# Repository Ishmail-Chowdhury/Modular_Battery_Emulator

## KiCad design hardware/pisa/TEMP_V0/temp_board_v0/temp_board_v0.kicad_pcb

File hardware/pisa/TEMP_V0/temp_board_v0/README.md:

# Pisa temperature card — TEMP-LAYOUT-1

Open `temp_board_v0.kicad_pro` in KiCad 10. The modern schematic and the **two-layer PCB** are synchronized with the selected temperature BOM. The board has **0 layout errors, 0 unrouted connections and 0 schematic-parity issues**, with 53 inherited library-definition warnings on retained footprints. ERC has 0 errors and 235 inherited off-grid drawing warnings. No rules were newly disabled.

All 34 fitted components are accounted for; no components or external mux were added. C2/U1/U3/U8 replacement footprints are installed and routed. Five components were relocated: C2, J6, C4, C9 and C11. The original card edge and outline are unchanged. J6 and the other optional headers remain DNP.

Readback of all eight DAC output voltages uses U1's internal analog selector and the populated bus-2 links R12/R18/R20. Temperature MISO exits **M1.34**, separate from CVE mux MISO on M1.33. For two boards, the two temperature returns must use separate FPGA inputs. No card/backplane patch wiring is required. The current Arty prototype has no temperature controller or pin allocation yet.

Current review: repository-root `docs/TEMPERATURE_LAYOUT_READBACK_2026_11_17.md`. Component datasheets and original-design discrepancies: `docs/TEMPERATURE_SCHEMATIC_REVIEW_2026_11_17.md` (historical schematic phase). Machine-readable checks and the BOM snapshot are in `docs/verification/temperature_layout_2026_11_17/`.

Run `tools/verify_temperature_layout.py` with KiCad's bundled Python. It requires the design folder, `--baseline-board`, `--baseline-netlist`, `--baseline-drc`, `--backplane`, `--bom`, `--output`, and optionally `--cli`. The documented baseline files in the verification folder allow the checks to be repeated.

This revision has not been fabricated or bench-qualified. Check actual connector/rack fit, including C2's 16 mm height, and qualify the CMU input bias, temperature curve and SPI timing during bring-up.

Original hardware author: University of Pisa Battery Lab. Baseline commit `a0d4499b8810e432f862b3f266d868523a92c2fc`; repository-root `TEMP_V0.rar` is retained unchanged. `legacy_reference/` preserves original source and stale purchasing exports; those exports are not the current BOM or fabrication package.

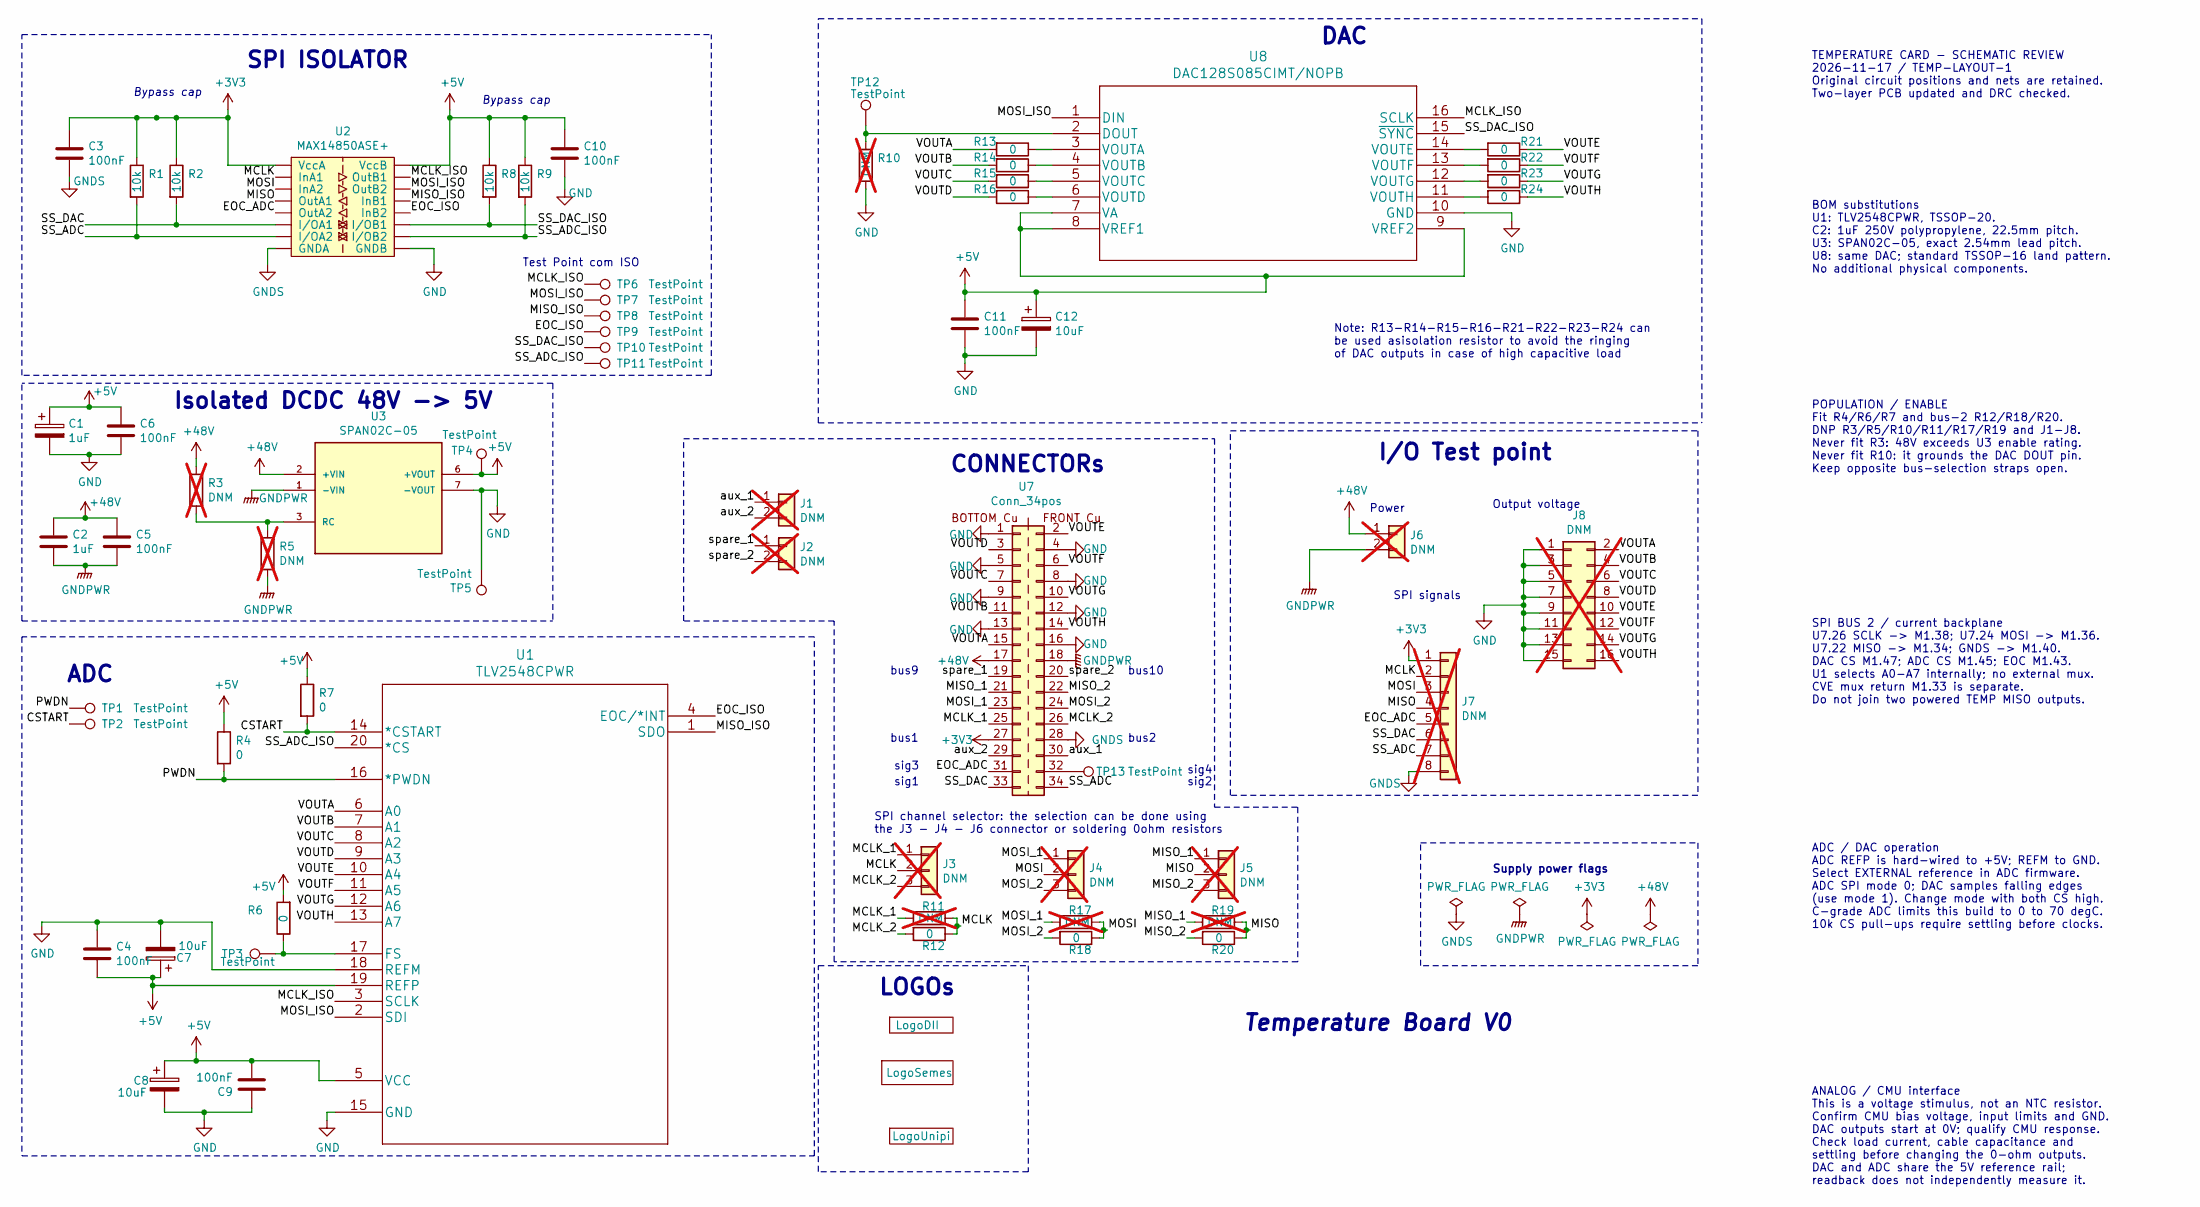
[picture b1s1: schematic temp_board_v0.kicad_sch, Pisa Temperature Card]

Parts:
C1: 1uF; CP_Elec_4x5.4; Rating 1uF / 50V; MPN 865060640001; JLCPCB C2163595
C2: 1uF; C_Rect_L26.5mm_W7.0mm_P22.50mm_MKS4; Rating 1uF / 250V PP; MPN R75IN410050H4J; JLCPCB C3787691
C3, C4, C6, C9, C10, C11: 100nF; C_0603_1608Metric_Pad1.08x0.95mm_HandSolder; Rating 100nF / 50V; MPN CC0603KRX7R9BB104; JLCPCB C14663
C5: 100nF; C_0805_2012Metric_Pad1.18x1.45mm_HandSolder; Rating 100nF / 100V; MPN CL21B104KCFNNNE; JLCPCB C28233
C7, C8, C12: 10uF; CP_Elec_4x5.4; Rating 10uF / 25V; MPN 865080440002; JLCPCB C2163477
J1, J2, J6: DNM; PinHeader_1x02_P2.54mm_Vertical; not fitted
J3, J4, J5: DNM; PinHeader_1x03_P2.54mm_Vertical; not fitted
J7: DNM; PinHeader_1x08_P2.54mm_Vertical; not fitted
J8: DNM; PinHeader_2x08_P2.54mm_Vertical; not fitted
R1, R2, R8, R9: 10k; R_0805_2012Metric_Pad1.20x1.40mm_HandSolder; MPN 0805W8F1002T5E; JLCPCB C17414
R3, R5, R10, R11, R17, R19: DNM; R_0805_2012Metric_Pad1.20x1.40mm_HandSolder; not fitted
R4, R6, R7, R12, R13, R14, R15, R16, R18, R20, R21, R22, R23, R24: 0; R_0805_2012Metric_Pad1.20x1.40mm_HandSolder; MPN 0805W8F0000T5E; JLCPCB C17477
TP1, TP2, TP3, TP4, TP5, TP6, TP7, TP8, TP9, TP10, TP11, TP12, TP13: TestPoint; PinHeader_1x01_P2.54mm_Vertical
U1: TLV2548CPWR; TSSOP-20_4.4x6.5mm_P0.65mm; MPN TLV2548CPWR; JLCPCB C2670506
U2: MAX14850ASE+; SOIC-16_3.9x9.9mm_P1.27mm; MPN MAX14850ASE+; Digikey PN MAX14850ASE+-ND
U3: SPAN02C-05; SPAN02C-05_SIP-8; PARTREV 1.0; JLCPCB C6681122
U4: LogoSemes; logo_semeslab_new_2
U5: LogoDII; logo_dii
U6: LogoUnipi; logo_cherubino
U7: Conn_34pos; Conn_34pos_Board
U8: DAC128S085CIMT/NOPB; TSSOP-16_4.4x5mm_P0.65mm; MPN DAC128S085CIMT/NOPB; JLCPCB C1554478

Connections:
+3V3: C3.1, J7.1, R1.1, R2.1, U2.1 (VccA), U7.27
+5V: C1.1, C4.2, C6.1, C7.1, C8.1, C9.2, C10.1, C11.1, C12.1, R4.1, R6.2, R7.1, R8.1, R9.1, TP4.1, U1.5 (VCC), U1.19 (REFP), U2.16 (VccB), U3.6 (+VOUT), U8.7 (VA), U8.8 (VREF1), U8.9 (VREF2)
+48V: C2.1, C5.1, J6.1, R3.1, U3.2 (+VIN), U7.17
/CSTART: R7.2, TP2.1, U1.14 (*CSTART)
/EOC_ADC: J7.5, U2.5 (OutA2), U7.31
/EOC_ISO: TP9.1, U1.4 (EOC/*INT), U2.12 (InB2)
/MCLK: J3.2, J7.2, R11.1, R12.1, U2.2 (InA1)
/MCLK_1: J3.1, R11.2, U7.25
/MCLK_2: J3.3, R12.2, U7.26
/MCLK_ISO: TP6.1, U1.3 (SCLK), U2.15 (OutB1), U8.16 (SCLK)
/MISO: J5.2, J7.4, R19.1, R20.1, U2.4 (OutA1)
/MISO_1: J5.1, R19.2, U7.21
/MISO_2: J5.3, R20.2, U7.22
/MISO_ISO: TP8.1, U1.1 (SDO), U2.13 (InB1)
/MOSI: J4.2, J7.3, R17.1, R18.1, U2.3 (InA2)
/MOSI_1: J4.1, R17.2, U7.23
/MOSI_2: J4.3, R18.2, U7.24
/MOSI_ISO: TP7.1, U1.2 (SDI), U2.14 (OutB2), U8.1 (DIN)
/PWDN: R4.2, TP1.1, U1.16 (*PWDN)
/SS_ADC: J7.7, R1.2, U2.7 (I/OA2), U7.34
/SS_ADC_ISO: R9.2, TP11.1, U1.20 (*CS), U2.10 (I/OB2)
/SS_DAC: J7.6, R2.2, U2.6 (I/OA1), U7.33
/SS_DAC_ISO: R8.2, TP10.1, U2.11 (I/OB1), U8.15 (~SYNC)
/VOUTA: J8.2, R13.2, U1.6 (A0), U7.15
/VOUTB: J8.4, R14.2, U1.7 (A1), U7.11
/VOUTC: J8.6, R15.2, U1.8 (A2), U7.7
/VOUTD: J8.8, R16.2, U1.9 (A3), U7.3
/VOUTE: J8.10, R21.1, U1.10 (A4), U7.2
/VOUTF: J8.12, R22.1, U1.11 (A5), U7.6
/VOUTG: J8.14, R23.1, U1.12 (A6), U7.10
/VOUTH: J8.16, R24.1, U1.13 (A7), U7.14
/aux_1: J1.1, U7.30
/aux_2: J1.2, U7.29
/spare_1: J2.1, U7.19
/spare_2: J2.2, U7.20
GND: C1.2, C4.1, C6.2, C7.2, C8.2, C9.1, C10.2, C11.2, C12.2, J8.1, J8.3, J8.5, J8.7, J8.9, J8.11, J8.13, J8.15, R10.2, TP5.1, U1.15 (GND), U1.18 (REFM), U2.9 (GNDB), U3.7 (-VOUT), U7.1, U7.4, U7.5, U7.8, U7.9, U7.12, U7.13, U7.16, U8.10 (GND)
GNDPWR: C2.2, C5.2, J6.2, R5.2, U3.1 (-VIN), U7.18
GNDS: C3.2, J7.8, U2.8 (GNDA), U7.28
unnamed: TP13.1, U7.32
unnamed: R6.1, TP3.1, U1.17 (FS)
unnamed: R3.2, R5.1, U3.3 (RC)
unnamed: R10.1, TP12.1, U8.2 (DOUT)
unnamed: R13.1, U8.3 (VOUTA)
unnamed: R14.1, U8.4 (VOUTB)
unnamed: R15.1, U8.5 (VOUTC)
unnamed: R16.1, U8.6 (VOUTD)
unnamed: R21.2, U8.14 (VOUTE)
unnamed: R22.2, U8.13 (VOUTF)
unnamed: R23.2, U8.12 (VOUTG)
unnamed: R24.2, U8.11 (VOUTH)

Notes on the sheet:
bus1
Test Point com ISO
Output voltage
Bypass cap
Temperature Board V0
bus9
sig1
LOGOs
bus2
Note: R13-R14-R15-R16-R21-R22-R23-R24 can be used asisolation resistor to avoid the ringing of DAC outputs in case of high capacitive load
I/O Test point
SPI ISOLATOR
sig2
SPI signals
sig3
CONNECTORs
bus10
SPI channel selector: the selection can be done using the J3 - J4 - J6 connector or soldering 0ohm resistors
Power
Isolated DCDC 48V -> 5V
Supply power flags
ADC
sig4
DAC
TEMPERATURE CARD - SCHEMATIC REVIEW 2026-11-17 / TEMP-LAYOUT-1 Original circuit positions and nets are retained. Two-layer PCB updated and DRC checked.
BOM substitutions U1: TLV2548CPWR, TSSOP-20. C2: 1uF 250V polypropylene, 22.5mm pitch. U3: SPAN02C-05, exact 2.54mm lead pitch. U8: same DAC; standard TSSOP-16 land pattern. No additional physical components.
POPULATION / ENABLE Fit R4/R6/R7 and bus-2 R12/R18/R20. DNP R3/R5/R10/R11/R17/R19 and J1-J8. Never fit R3: 48V exceeds U3 enable rating. Never fit R10: it grounds the DAC DOUT pin. Keep opposite bus-selection straps open.
SPI BUS 2 / current backplane U7.26 SCLK -> M1.38; U7.24 MOSI -> M1.36. U7.22 MISO -> M1.34; GNDS -> M1.40. DAC CS M1.47; ADC CS M1.45; EOC M1.43. U1 selects A0-A7 internally; no external mux. CVE mux return M1.33 is separate. Do not join two powered TEMP MISO outputs.
ADC / DAC operation ADC REFP is hard-wired to +5V; REFM to GND. Select EXTERNAL reference in ADC firmware. ADC SPI mode 0; DAC samples falling edges (use mode 1). Change mode with both CS high. C-grade ADC limits this build to 0 to 70 degC. 10k CS pull-ups require settling before clocks.
ANALOG / CMU interface This is a voltage stimulus, not an NTC resistor. Confirm CMU bias voltage, input limits and GND. DAC outputs start at 0V; qualify CMU response. Check load current, cable capacitance and settling before changing the 0-ohm outputs. DAC and ADC share the 5V reference rail; readb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

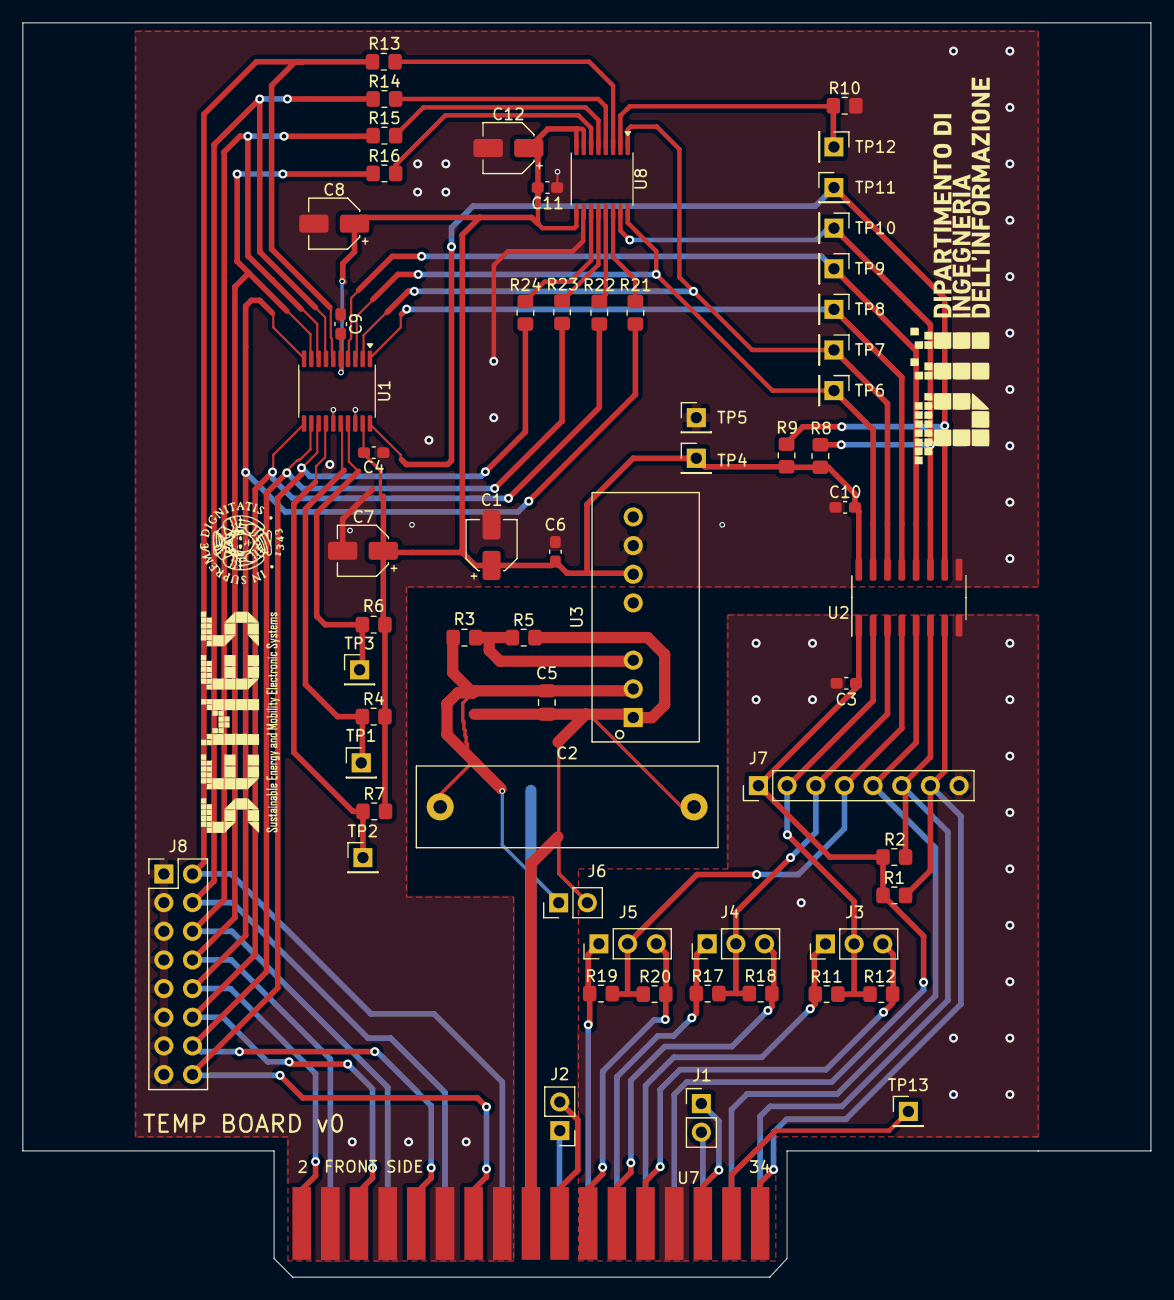
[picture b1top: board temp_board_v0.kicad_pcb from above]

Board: 2 copper layers, 100.0 x 111.2 mm, 65 parts (0 on the bottom side), 50 nets.

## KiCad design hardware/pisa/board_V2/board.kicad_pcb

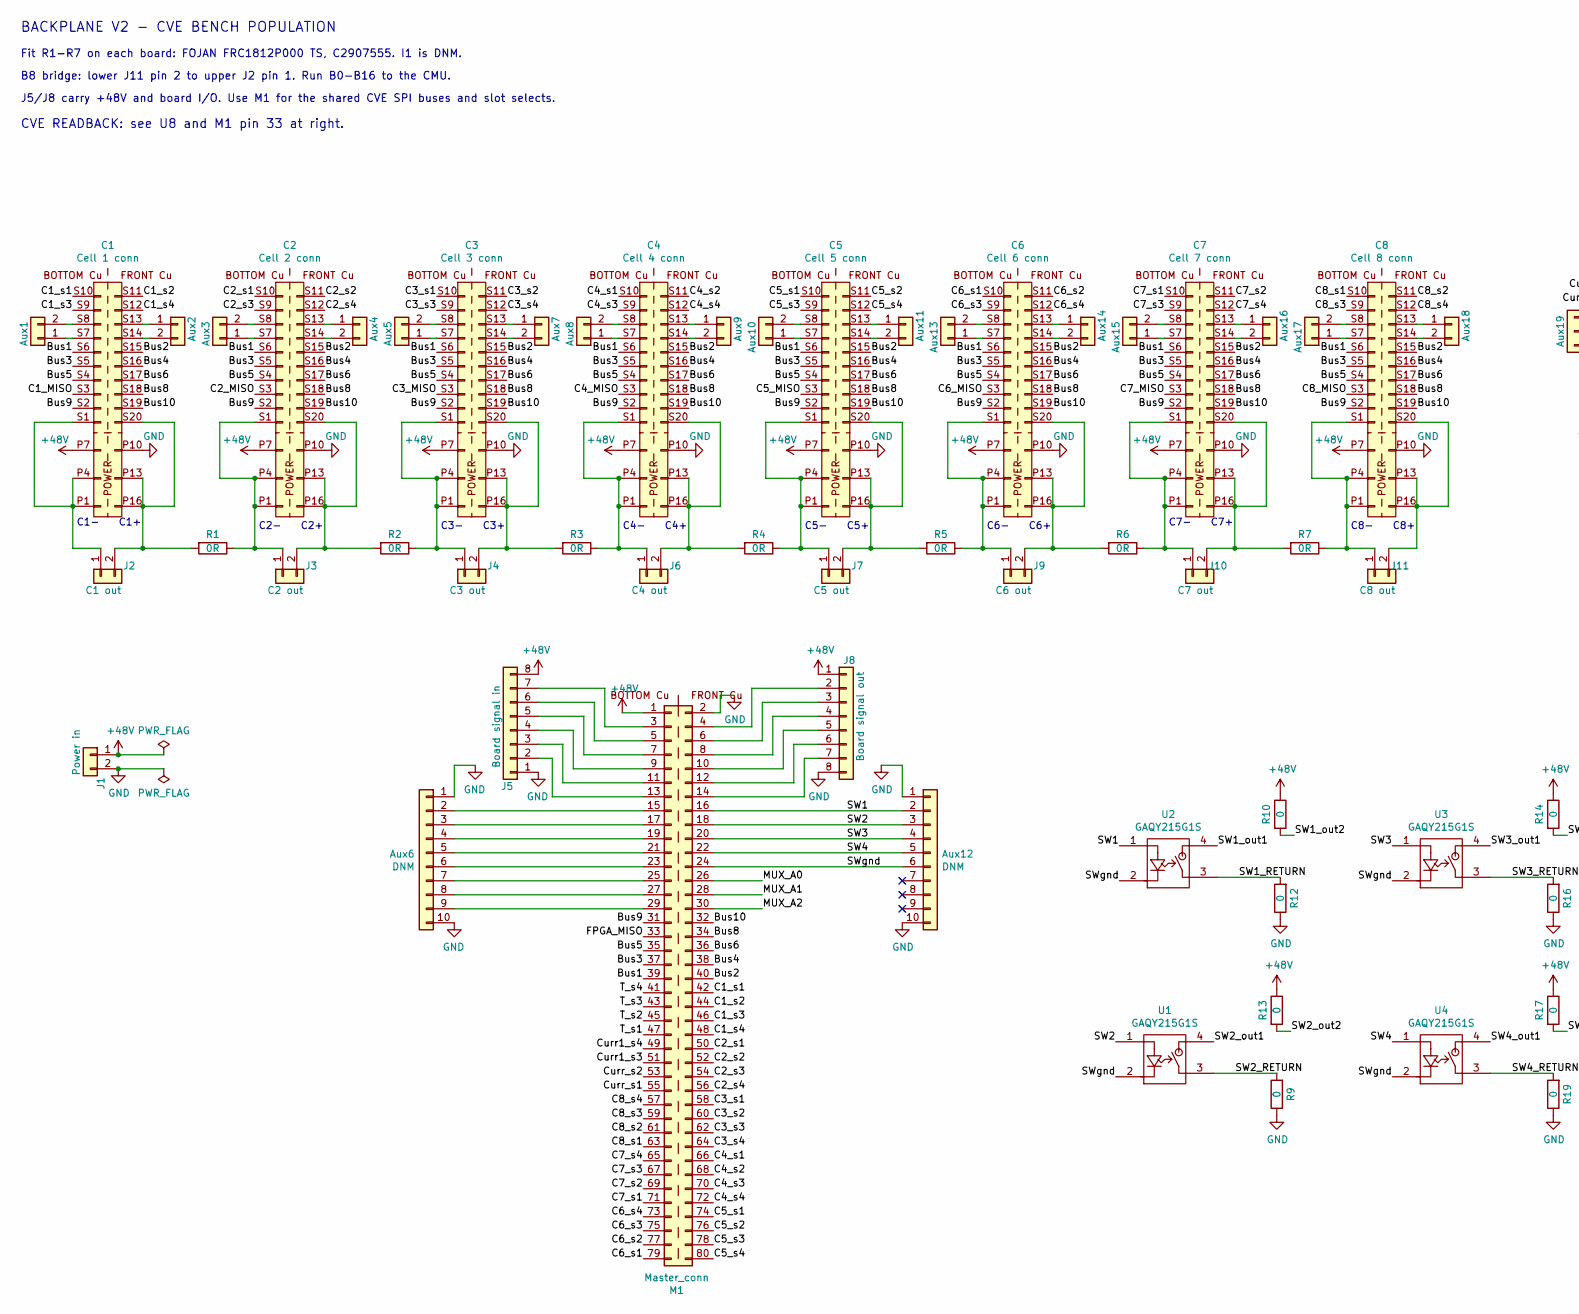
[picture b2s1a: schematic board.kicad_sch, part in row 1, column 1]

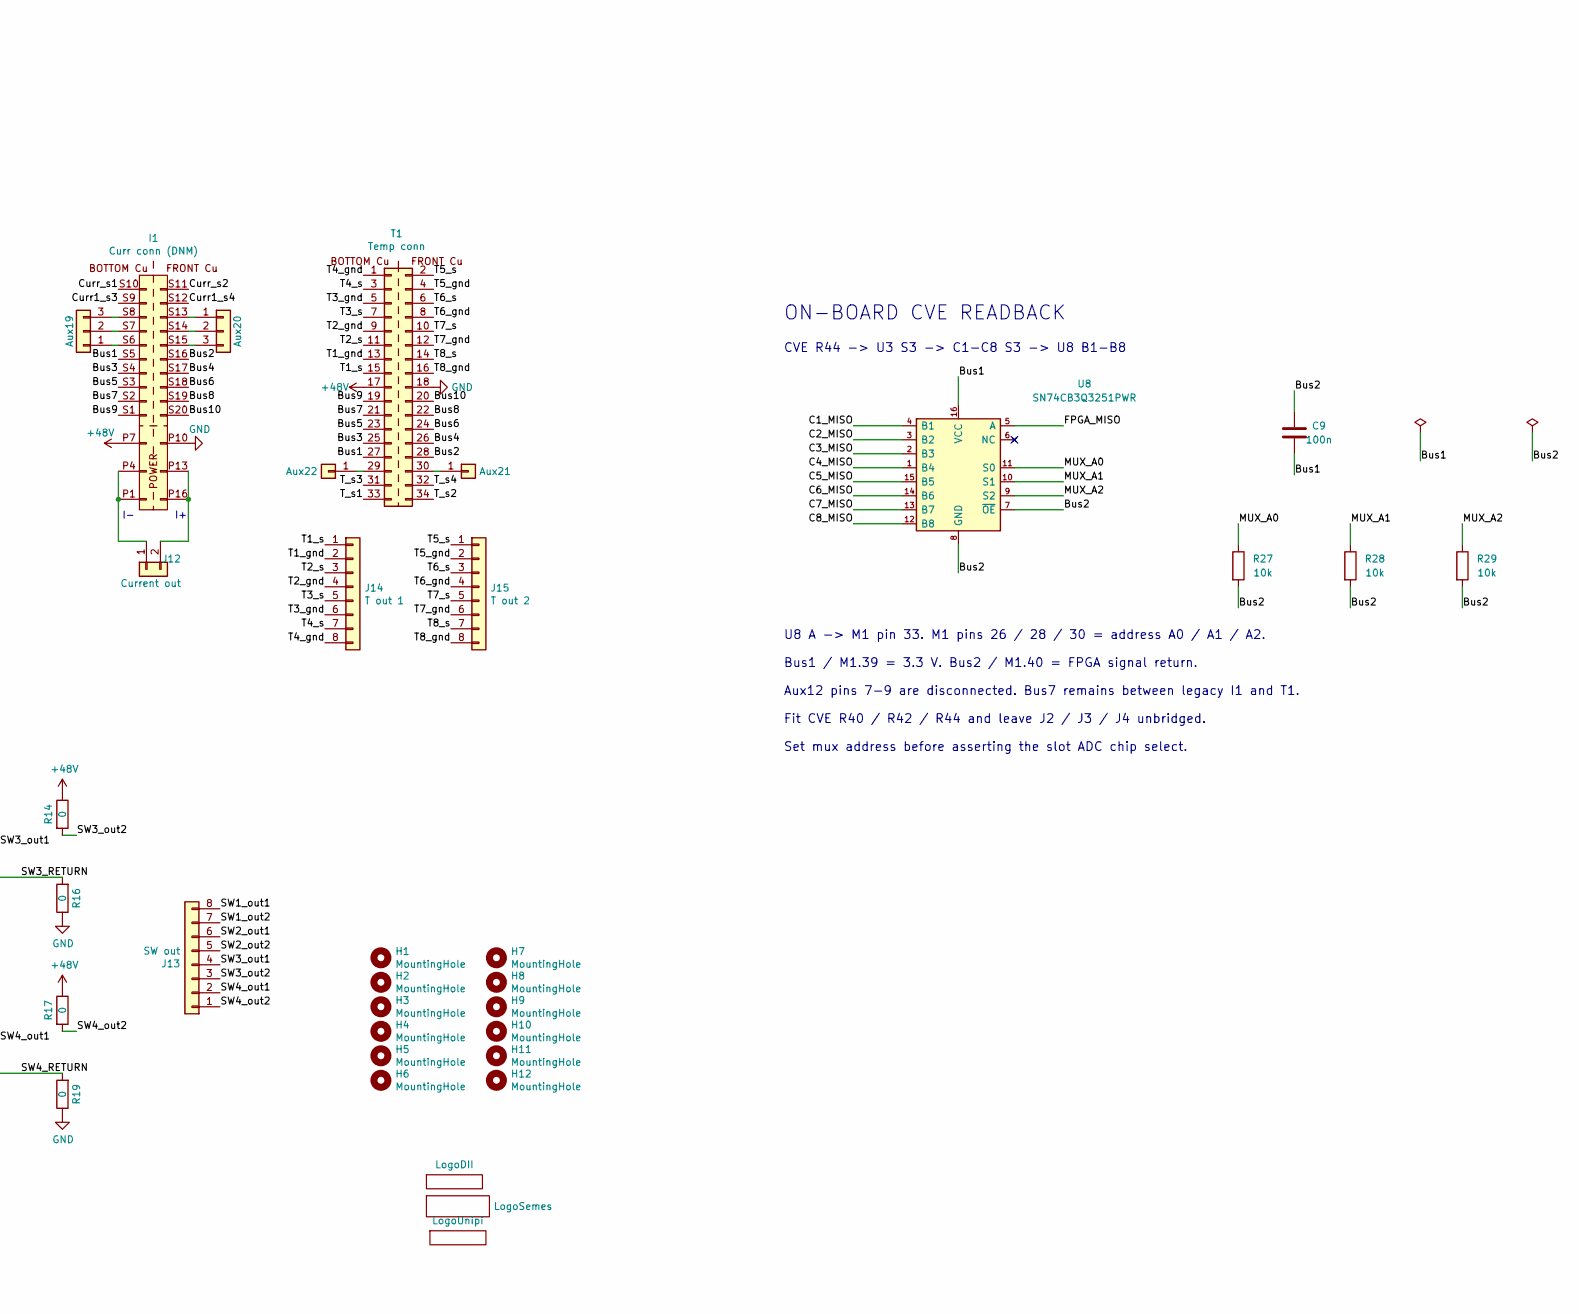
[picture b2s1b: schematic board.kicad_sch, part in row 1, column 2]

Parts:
Aux1, Aux2, Aux3, Aux4, Aux5, Aux7, Aux8, Aux9, Aux10, Aux11, Aux13, Aux14, Aux15, Aux16, Aux17, Aux18: DNM; Socket_Strip_Straight_1x02_Pitch2.54mm
Aux6, Aux12: DNM; Socket_Strip_Straight_1x10_Pitch2.54mm
Aux19, Aux20: DNM; Socket_Strip_Straight_1x03_Pitch2.54mm
Aux21, Aux22: DNM; Socket_Strip_Straight_1x01_Pitch2.54mm
C1: Cell 1 conn; Conn_26pos_Head
C2: Cell 2 conn; Conn_26pos_Head
C3: Cell 3 conn; Conn_26pos_Head
C4: Cell 4 conn; Conn_26pos_Head
C5: Cell 5 conn; Conn_26pos_Head
C6: Cell 6 conn; Conn_26pos_Head
C7: Cell 7 conn; Conn_26pos_Head
C8: Cell 8 conn; Conn_26pos_Head
C9: 100n; C_0603_1608Metric; MPN CL10B104KB8NNNC; JLCPCB C1591
H1, H2, H3, H4, H5, H6, H7, H8, H9, H10, H11, H12: MountingHole; MountingHole_3.2mm_M3
I1: Curr conn (DNM); Conn_26pos_Head
J1: Power in; 691137710002; JLCPCB C474881
J2: C1 out; 691137710002; JLCPCB C474881
J3: C2 out; 691137710002; JLCPCB C474881
J4: C3 out; 691137710002; JLCPCB C474881
J5: Board signal in; 691402910008B; JLCPCB C915917
J6: C4 out; 691137710002; JLCPCB C474881
J7: C5 out; 691137710002; JLCPCB C474881
J8: Board signal out; 691402910008B; JLCPCB C915917
J9: C6 out; 691137710002; JLCPCB C474881
J10: C7 out; 691137710002; JLCPCB C474881
J11: C8 out; 691137710002; JLCPCB C474881
J12: Current out; 691137710002; JLCPCB C474881
J13: SW out; 691402910008B; JLCPCB C915917
J14: T out 1; 691402910008B; JLCPCB C915917
J15: T out 2; 691402910008B; JLCPCB C915917
M1: Master_conn; Conn_80pos_Head
R1, R2, R3, R4, R5, R6, R7: 0R; R_1812_HandSoldering; JLCPCB C2907555
R9, R10, R12, R13, R14, R16, R17, R19: 0; R_0805_HandSoldering; JLCPCB C17477
R27, R28, R29: 10k; R_0603_1608Metric; MPN 0603WAF1002T5E; JLCPCB C25804
T1: Temp conn; Conn_34pos_Head; JLCPCB C4801357
U1, U2, U3, U4: GAQY215G1S; GAQY215G1S_SOP-4; JLCPCB C22385004
U5: LogoDII; logo_dii
U6: LogoSemes; logo_semeslab_new_2
U7: LogoUnipi; logo_cherubino
U8: SN74CB3Q3251PWR; TSSOP-16_4.4x5mm_P0.65mm; MPN SN74CB3Q3251PWR

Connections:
+48V: C1.P7, C2.P7, C3.P7, C4.P7, C5.P7, C6.P7, C7.P7, C8.P7, I1.P7, J1.1, J5.8, J8.1, M1.1, R10.1, R13.1, R14.1, R17.1, T1.17
/Bus1: C1.S6, C2.S6, C3.S6, C4.S6, C5.S6, C6.S6, C7.S6, C8.S6, C9.2, I1.S5, M1.39, T1.27, U8.16 (VCC)
/Bus2: C1.S15, C2.S15, C3.S15, C4.S15, C5.S15, C6.S15, C7.S15, C8.S15, C9.1, I1.S16, M1.40, R27.2, R28.2, R29.2, T1.28, U8.7 (~OE), U8.8 (GND)
/Bus3: C1.S5, C2.S5, C3.S5, C4.S5, C5.S5, C6.S5, C7.S5, C8.S5, I1.S4, M1.37, T1.25
/Bus4: C1.S16, C2.S16, C3.S16, C4.S16, C5.S16, C6.S16, C7.S16, C8.S16, I1.S17, M1.38, T1.26
/Bus5: C1.S4, C2.S4, C3.S4, C4.S4, C5.S4, C6.S4, C7.S4, C8.S4, I1.S3, M1.35, T1.23
/Bus6: C1.S17, C2.S17, C3.S17, C4.S17, C5.S17, C6.S17, C7.S17, C8.S17, I1.S18, M1.36, T1.24
/Bus7: I1.S2, T1.21
/Bus8: C1.S18, C2.S18, C3.S18, C4.S18, C5.S18, C6.S18, C7.S18, C8.S18, I1.S19, M1.34, T1.22
/Bus9: C1.S2, C2.S2, C3.S2, C4.S2, C5.S2, C6.S2, C7.S2, C8.S2, I1.S1, M1.31, T1.19
/Bus10: C1.S19, C2.S19, C3.S19, C4.S19, C5.S19, C6.S19, C7.S19, C8.S19, I1.S20, M1.32, T1.20
/C1_MISO: C1.S3, U8.4 (B1)
/C1_s1: C1.S10, M1.42
/C1_s2: C1.S11, M1.44
/C1_s3: C1.S9, M1.46
/C1_s4: C1.S12, M1.48
/C2_MISO: C2.S3, U8.3 (B2)
/C2_s1: C2.S10, M1.50
/C2_s2: C2.S11, M1.52
/C2_s3: C2.S9, M1.54
/C2_s4: C2.S12, M1.56
/C3_MISO: C3.S3, U8.2 (B3)
/C3_s1: C3.S10, M1.58
/C3_s2: C3.S11, M1.60
/C3_s3: C3.S9, M1.62
/C3_s4: C3.S12, M1.64
/C4_MISO: C4.S3, U8.1 (B4)
/C4_s1: C4.S10, M1.66
/C4_s2: C4.S11, M1.68
/C4_s3: C4.S9, M1.70
/C4_s4: C4.S12, M1.72
/C5_MISO: C5.S3, U8.15 (B5)
/C5_s1: C5.S10, M1.74
/C5_s2: C5.S11, M1.76
/C5_s3: C5.S9, M1.78
/C5_s4: C5.S12, M1.80
/C6_MISO: C6.S3, U8.14 (B6)
/C6_s1: C6.S10, M1.79
/C6_s2: C6.S11, M1.77
/C6_s3: C6.S9, M1.75
/C6_s4: C6.S12, M1.73
/C7_MISO: C7.S3, U8.13 (B7)
/C7_s1: C7.S10, M1.71
/C7_s2: C7.S11, M1.69
/C7_s3: C7.S9, M1.67
/C7_s4: C7.S12, M1.65
/C8_MISO: C8.S3, U8.12 (B8)
/C8_s1: C8.S10, M1.63
/C8_s2: C8.S11, M1.61
/C8_s3: C8.S9, M1.59
/C8_s4: C8.S12, M1.57
/Curr1_s3: I1.S9, M1.51
/Curr1_s4: I1.S12, M1.49
/Curr_s1: I1.S10, M1.55
/Curr_s2: I1.S11, M1.53
/FPGA_MISO: M1.33, U8.5 (A)
/MUX_A0: M1.26, R27.1, U8.11 (S0)
/MUX_A1: M1.28, R28.1, U8.10 (S1)
/MUX_A2: M1.30, R29.1, U8.9 (S2)
/SW1: Aux12.2, M1.16, U2.1
/SW1_RETURN: R12.2, U2.3
/SW1_out1: J13.8, U2.4
/SW1_out2: J13.7, R10.2
/SW2: Aux12.3, M1.18, U1.1
/SW2_RETURN: R9.2, U1.3
/SW2_out1: J13.6, U1.4
/SW2_out2: J13.5, R13.2
/SW3: Aux12.4, M1.20, U3.1
/SW3_RETURN: R16.2, U3.3
/SW3_out1: J13.4, U3.4
/SW3_out2: J13.3, R14.2
/SW4: Aux12.5, M1.22, U4.1
/SW4_RETURN: R19.2, U4.3
/SW4_out1: J13.2, U4.4
/SW4_out2: J13.1, R17.2
/SWgnd: Aux12.6, M1.24, U1.2, U2.2, U3.2, U4.2
/T1_gnd: J14.2, T1.13
/T1_s: J14.1, T1.15
/T2_gnd: J14.4, T1.9
/T2_s: J14.3, T1.11
/T3_gnd: J14.6, T1.5
/T3_s: J14.5, T1.7
/T4_gnd: J14.8, T1.1
/T4_s: J14.7, T1.3
/T5_gnd: J15.2, T1.4
/T5_s: J15.1, T1.2
/T6_gnd: J15.4, T1.8
/T6_s: J15.3, T1.6
/T7_gnd: J15.6, T1.12
/T7_s: J15.5, T1.10
/T8_gnd: J15.8, T1.16
/T8_s: J15.7, T1.14
/T_s1: M1.47, T1.33
/T_s2: M1.45, T1.34
/T_s3: M1.43, T1.31
/T_s4: M1.41, T1.32
GND: Aux6.1, Aux6.10, Aux12.1, Aux12.10, C1.P10, C2.P10, C3.P10, C4.P10, C5.P10, C6.P10, C7.P10, C8.P10, I1.P10, J1.2, J5.1, J8.8, M1.2, R9.1, R12.1, R16.1, R19.1, T1.18
unnamed: Aux1.1, C1.S7
unnamed: Aux1.2, C1.S8
unnamed: Aux2.1, C1.S13
unnamed: Aux2.2, C1.S14
unnamed: Aux3.1, C2.S7
unnamed: Aux3.2, C2.S8
unnamed: Aux4.1, C2.S13
unnamed: Aux4.2, C2.S14
unnamed: Aux5.1, C3.S7
unnamed: Aux5.2, C3.S8
unnamed: Aux6.2, M1.15
unnamed: Aux6.3, M1.17
unnamed: Aux6.4, M1.19
unnamed: Aux6.5, M1.21
unnamed: Aux6.6, M1.23
unnamed: Aux6.7, M1.25
unnamed: Aux6.8, M1.27
unnamed: Aux6.9, M1.29
unnamed: Aux7.1, C3.S13
unnamed: Aux7.2, C3.S14
unnamed: Aux8.1, C4.S7
unnamed: Aux8.2, C4.S8
unnamed: Aux9.1, C4.S13
unnamed: Aux9.2, C4.S14
unnamed: Aux10.1, C5.S7
unnamed: Aux10.2, C5.S8
unnamed: Aux11.1, C5.S13
unnamed: Aux11.2, C5.S14
unnamed: Aux13.1, C6.S7
unnamed: Aux13.2, C6.S8
unnamed: Aux14.1, C6.S13
unnamed: Aux14.2, C6.S14
unnamed: Aux15.1, C7.S7
unnamed: Aux15.2, C7.S8
unnamed: Aux16.1, C7.S13
unnamed: Aux16.2, C7.S14
unnamed: Aux17.1, C8.S7
unnamed: Aux17.2, C8.S8
unnamed: Aux18.1, C8.S13
unnamed: Aux18.2, C8.S14
unnamed: Aux19.1, I1.S6
unnamed: Aux19.2, I1.S7
unnamed: Aux19.3, I1.S8
unnamed: Aux20.1, I1.S13
unnamed: Aux20.2, I1.S14
unnamed: Aux20.3, I1.S15
unnamed: Aux21.1, T1.30
unnamed: Aux22.1, T1.29
unnamed: C1.P1, C1.P4, C1.S1, J2.1
unnamed: C1.P13, C1.P16, C1.S20, J2.2, R1.2
unnamed: C2.P1, C2.P4, C2.S1, J3.1, R1.1
unnamed: C2.P13, C2.P16, C2.S20, J3.2, R2.2
unnamed: C3.P1, C3.P4, C3.S1, J4.1, R2.1
unnamed: C3.P13, C3.P16, C3.S20, J4.2, R3.2
unnamed: J5.2, M1.13
unnamed: J5.3, M1.11
unnamed: J5.4, M1.9
unnamed: J5.5, M1.7
unnamed: J5.6, M1.5
unnamed: J5.7, M1.3
unnamed: C4.P1, C4.P4, C4.S1, J6.1, R3.1
unnamed: C4.P13, C4.P16, C4.S20, J6.2, R4.2
unnamed: C5.P1, C5.P4, C5.S1, J7.1, R4.1
unnamed: C5.P13, C5.P16, C5.S20, J7.2, R5.2
unnamed: J8.2, M1.4
unnamed: J8.3, M1.6
unnamed: J8.4, M1.8
unnamed: J8.5, M1.10
unnamed: J8.6, M1.12
unnamed: J8.7, M1.14
unnamed: C6.P1, C6.P4, C6.S1, J9.1, R5.1
unnamed: C6.P13, C6.P16, C6.S20, J9.2, R6.2
unnamed: C7.P1, C7.P4, C7.S1, J10.1, R6.1
unnamed: C7.P13, C7.P16, C7.S20, J10.2, R7.2
unnamed: C8.P1, C8.P4, C8.S1, J11.1, R7.1
unnamed: C8.P13, C8.P16, C8.S20, J11.2
unnamed: I1.P1, I1.P4, J12.1
unnamed: I1.P13, I1.P16, J12.2

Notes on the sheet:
C2+
C7-
C4+
C8-
C3+
C7+
C6+
C1-
C2-
C4-
C3-
BACKPLANE V2 - CVE BENCH POPULATION
C5-
B8 bridge: lower J11 pin 2 to upper J2 pin 1. Run B0-B16 to the CMU.
C5+
C8+
Fit R1-R7 on each board: FOJAN FRC1812P000 TS, C2907555. I1 is DNM.
C6-
J5/J8 carry +48V and board I/O. Use M1 for the shared CVE SPI buses and slot selects.
C1+
ON-BOARD CVE READBACK
CVE R44 -> U3 S3 -> C1-C8 S3 -> U8 B1-B8
U8 A -> M1 pin 33. M1 pins 26 / 28 / 30 = address A0 / A1 / A2.
Bus1 / M1.39 = 3.3 V. Bus2 / M1.40 = FPGA signal return.
Aux12 pins 7-9 are disconnected. Bus7 remains between legacy I1 and T1.
Fit CVE R40 / R42 / R44 and leave J2 / J3 / J4 unbridged.
Set mux address before asserting the slot ADC chip select.
CVE READBACK: see U8 and M1 pin 33 at right.

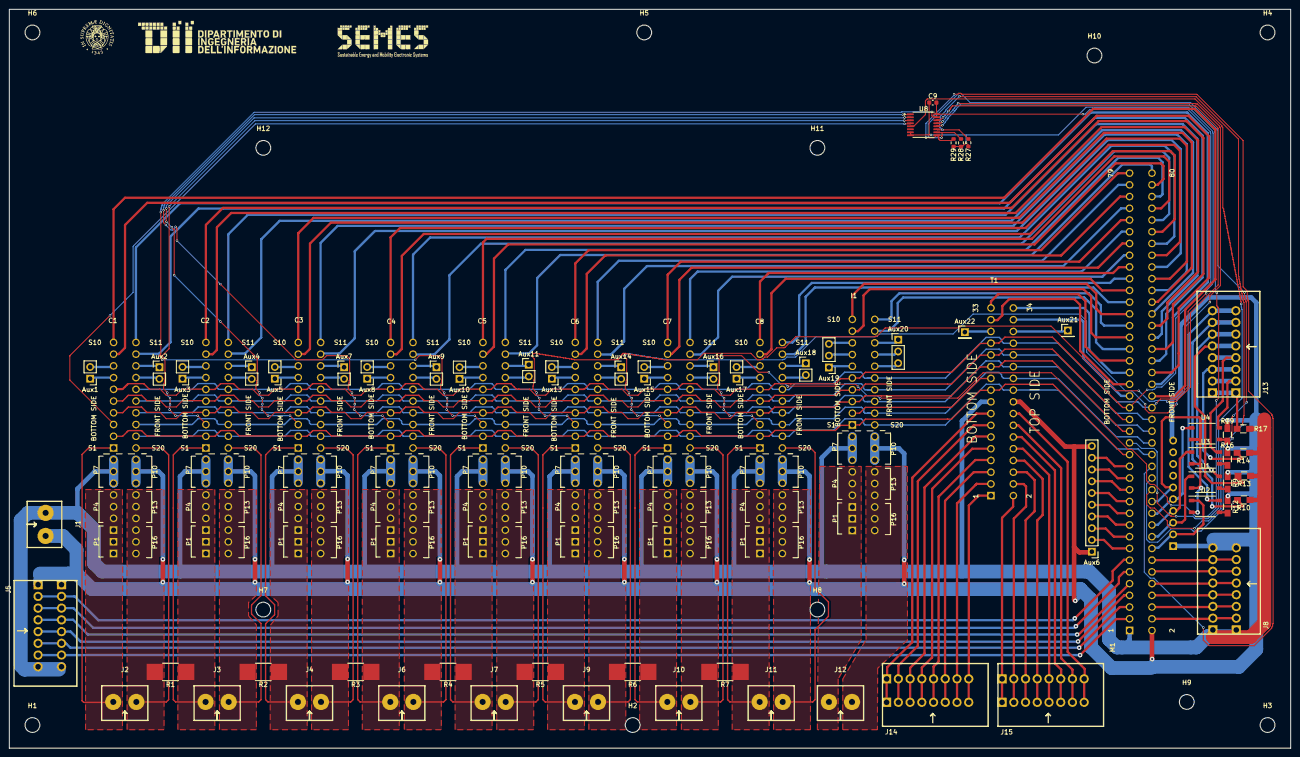
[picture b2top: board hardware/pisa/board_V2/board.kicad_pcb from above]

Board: 2 copper layers, 277.5 x 160.0 mm, 87 parts (1 on the bottom side), 175 nets.

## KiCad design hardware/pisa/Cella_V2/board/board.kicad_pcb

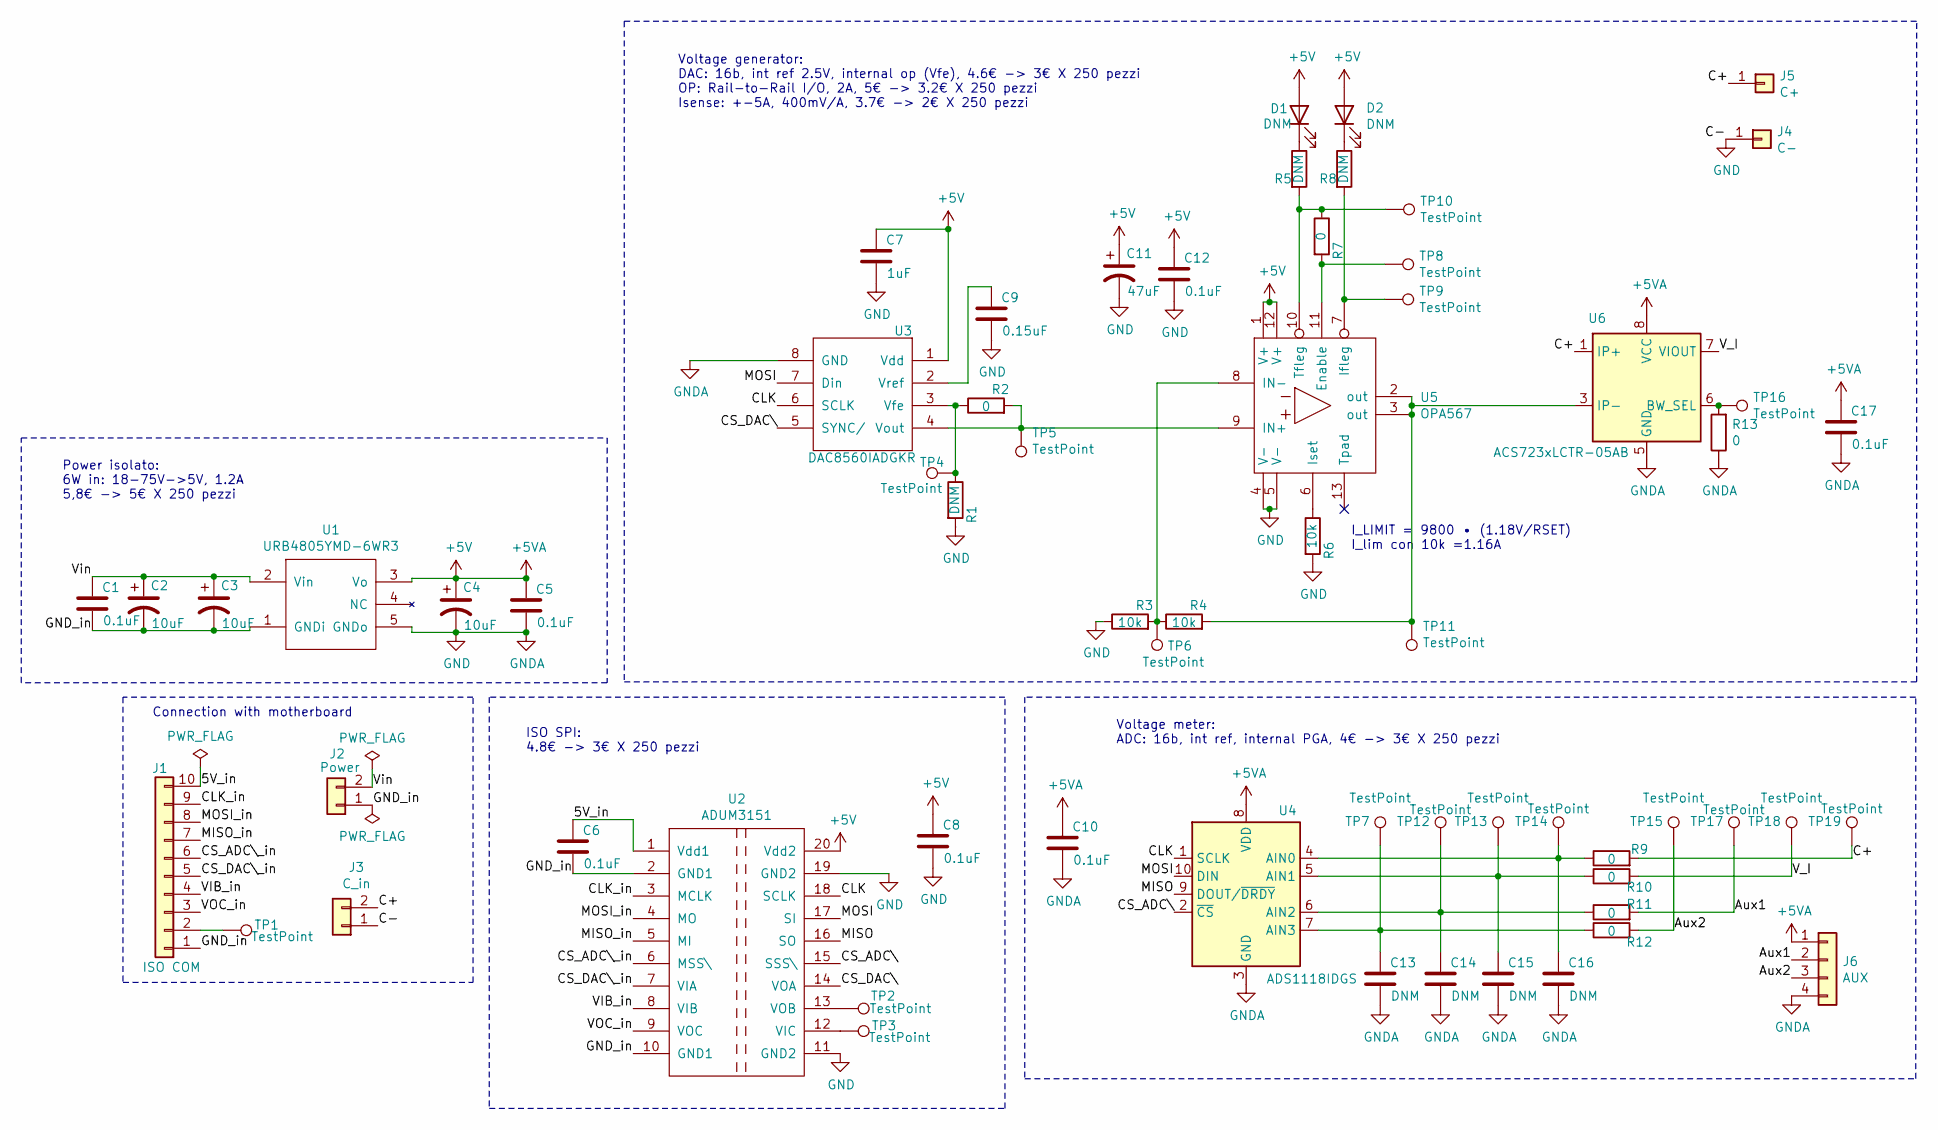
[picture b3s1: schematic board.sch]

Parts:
C1, C5, C6, C8, C10, C12, C17: 0.1uF; C_0805_HandSoldering; Digi 1276-6840-1-ND
C2, C3, C4: 10uF; CP_Elec_6.3x7.7; Digi 399-18132-1-ND
C7: 1uF; C_0805_HandSoldering; Digi 1276-6471-1-ND
C9: 0.15uF; C_0805_HandSoldering; Digi 1276-6476-1-ND
C11: 47uF; CP_Elec_10x10.5; Digi 493-9631-1-ND
C13, C14, C15, C16: DNM; C_0805_HandSoldering; Digi 1276-6840-1-ND
D1, D2: DNM; D_0805
J1: ISO COM; Pin_Header_Straight_1x10_Pitch2.54mm
J2: Power; Pin_Header_Straight_1x02_Pitch2.54mm
J3: C_in; Pin_Header_Straight_1x02_Pitch2.54mm
J4: C-; Banana_Jack_1Pin
J5: C+; Banana_Jack_1Pin
J6: AUX; Pin_Header_Straight_1x04_Pitch2.54mm
R1, R5, R8: DNM; C_0805_HandSoldering
R2, R7, R9, R10, R11, R12, R13: 0; C_0805_HandSoldering
R3, R4, R6: 10k; C_0805_HandSoldering; Digi P10KDACT-ND
TP1, TP2, TP3, TP4, TP5, TP6, TP7, TP8, TP9, TP10, TP11, TP12, TP13, TP14, TP15, TP16, TP17, TP18, TP19: TestPoint; Pin_Header_Straight_1x01_Pitch2.54mm
U1: URB4805YMD-6WR3; Digi 2725-URB4805YMD-6WR3-ND
U2: ADUM3151; SSOP-20_5.3x7.2mm_Pitch0.65mm; Digi ADUM3151BRSZ-RL7CT-ND
U3: DAC8560IADGKR; MSOP-8_3x3mm_Pitch0.65mm; Digi 296-49165-1-ND
U4: ADS1118IDGS; MSOP-10_3x3mm_Pitch0.5mm; Digi 296-38850-1-ND
U5: OPA567; Texas_S-PVQFN-N12_ThermalVias; Digi 296-18697-1-ND
U6: ACS723xLCTR-05AB; SOIC-8_3.9x4.9mm_Pitch1.27mm; Digi 620-1641-1-ND

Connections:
+5V: C4.1, C5.1, C7.1, C8.1, C10.1, C11.1, C12.1, C17.1, D1.2 (A), D2.2 (A), J6.1, U1.3 (Vo), U2.20 (Vdd2), U3.1 (Vdd), U4.8 (VDD), U5.1 (V+), U5.12 (V+), U6.8 (VCC)
/5V_in: C6.1, J1.10, U2.1 (Vdd1)
/Aux1: J6.2, R11.2, TP17.1
/Aux2: J6.3, R12.2, TP15.1
/C+: J3.2, J5.1, R9.2, TP19.1, U6.1 (IP+), U6.2 (IP+)
/CLK: U2.18 (SCLK), U3.6 (SCLK), U4.1 (SCLK)
/CLK_in: J1.9, U2.3 (MCLK)
/CS_ADC\: U2.15 (SSS\), U4.2 (~CS)
/CS_ADC\_in: J1.6, U2.6 (MSS\)
/CS_DAC\: U2.14 (VOA), U3.5 (SYNC/)
/CS_DAC\_in: J1.5, U2.7 (VIA)
/GND_in: C1.2, C2.2, C3.2, C6.2, J1.1, J2.1, U1.1 (GNDi), U2.2 (GND1), U2.10 (GND1)
/MISO: U2.16 (SO), U4.9 (DOUT/~DRDY)
/MISO_in: J1.7, U2.5 (MI)
/MOSI: U2.17 (SI), U3.7 (Din), U4.10 (DIN)
/MOSI_in: J1.8, U2.4 (MO)
/VIB_in: J1.4, U2.8 (VIB)
/VOC_in: J1.3, U2.9 (VOC)
/V_I: R10.2, TP18.1, U6.7 (VIOUT)
/Vin: C1.1, C2.1, C3.1, J2.2, U1.2 (Vin)
GND: C4.2, C5.2, C7.2, C8.2, C9.2, C10.2, C11.2, C12.2, C13.2, C14.2, C15.2, C16.2, C17.2, J3.1, J4.1, J6.4, R1.2, R3.1, R6.2, R13.1, U1.5 (GNDo), U2.11 (GND2), U2.19 (GND2), U3.8 (GND), U4.3 (GND), U5.4 (V-), U5.5 (V-), U6.5 (GND)
unnamed: C9.1, U3.2 (Vref)
unnamed: C13.1, R12.1, TP7.1, U4.7 (AIN3)
unnamed: C14.1, R11.1, TP12.1, U4.6 (AIN2)
unnamed: C15.1, R10.1, TP13.1, U4.5 (AIN1)
unnamed: C16.1, R9.1, TP14.1, U4.4 (AIN0)
unnamed: D1.1 (K), R5.1
unnamed: D2.1 (K), R8.1
unnamed: J1.2, TP1.1
unnamed: R1.1, R2.1, TP4.1, U3.3 (Vfe)
unnamed: R2.2, TP5.1, U3.4 (Vout), U5.9 (IN+)
unnamed: R3.2, R4.1, TP6.1, U5.8 (IN-)
unnamed: R4.2, TP11.1, U5.2 (out), U5.3 (out), U6.3 (IP-), U6.4 (IP-)
unnamed: R5.2, R7.1, TP10.1, U5.10 (Tfleg)
unnamed: R6.1, U5.6 (Iset)
unnamed: R7.2, TP8.1, U5.11 (Enable)
unnamed: R8.2, TP9.1, U5.7 (Ifleg)
unnamed: R13.2, TP16.1, U6.6 (BW_SEL)
unnamed: TP2.1, U2.13 (VOB)
unnamed: TP3.1, U2.12 (VIC)

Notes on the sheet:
I_LIMIT = 9800 • (1.18V/RSET) I_lim con 10k =1.16A
Power isolato: 6W in: 18-75V->5V, 1.2A 5,8€ -> 5€ X 250 pezzi
Voltage generator: DAC: 16b, int ref 2.5V, internal op (Vfe), 4.6€ -> 3€ X 250 pezzi OP: Rail-to-Rail I/O, 2A, 5€ -> 3.2€ X 250 pezzi Isense: +-5A, 400mV/A, 3.7€ -> 2€ X 250 pezzi
Voltage meter: ADC: 16b, int ref, internal PGA, 4€ -> 3€ X 250 pezzi
ISO SPI: 4.8€ -> 3€ X 250 pezzi
Connection with motherboard
